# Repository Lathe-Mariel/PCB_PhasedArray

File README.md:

# PCB_PhasedArray

 # BoM
デュアルＭＯＳＦＥＴ（Ｎｃｈ＋Ｎｃｈ）　３０Ｖ５Ａ　ＮＤＳ９９３６　（１０個入）
[NDS9936]

RoHS2未調査、または調査継続中。
ハーフブリッジゲートドライバ　ＩＲ２１５３１ＳＰＢＦＴＲ　ＯＳＣ　８－ＳＯＩＣ（２個入）
[IR21531SPBFTR]

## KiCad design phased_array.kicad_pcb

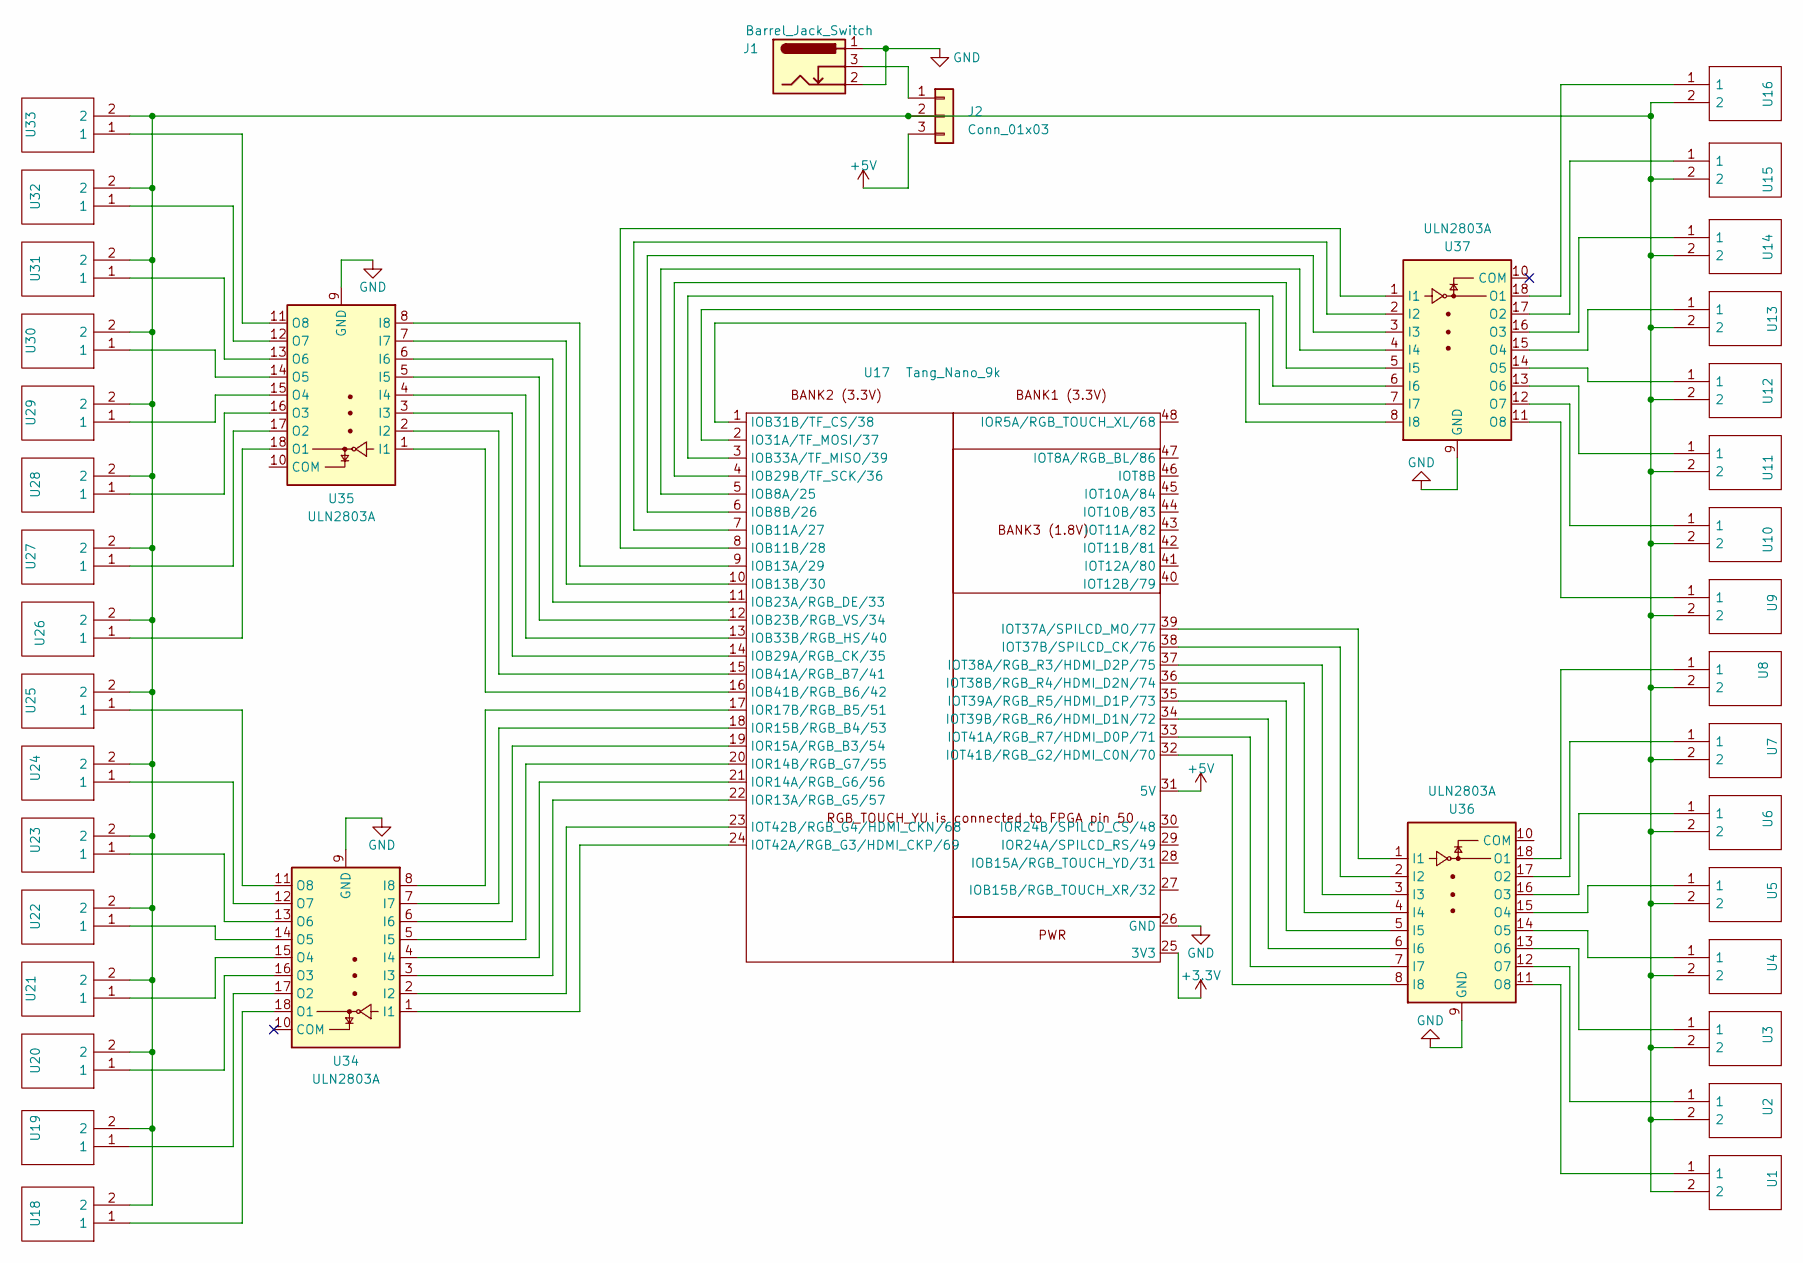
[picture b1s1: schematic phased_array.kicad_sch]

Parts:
J1: Barrel_Jack_Switch; BarrelJack_Horizontal
J2: Conn_01x03; PinHeader_1x03_P2.54mm_Vertical
U1, U2, U3, U4, U5, U6, U7, U8, U9, U10, U11, U12, U13, U14, U15, U16, U18, U19, U20, U21, U22, U23, U24, U25, U26, U27, U28, U29, U30, U31, U32, U33: CUSA-T80-18-2400-TH; CUSAT80182400TH; Manufacturer_Part_Number CUSA-T80-18-2400-TH
U17: Tang_Nano_9k; Tang Nano 9K
U34, U35, U36, U37: ULN2803A; DIP762W55P254L2286H480Q18N_with_solderjumper

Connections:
+3.3V: U17.25 (3V3)
+5V: J2.3, U17.31 (5V)
GND: J1.1, J1.2, U17.26 (GND), U34.9 (GND), U35.9 (GND), U36.9 (GND), U37.9 (GND)
unnamed: J1.3, J2.1
unnamed: J2.2, U1.2, U2.2, U3.2, U4.2, U5.2, U6.2, U7.2, U8.2, U9.2, U10.2, U11.2, U12.2, U13.2, U14.2, U15.2, U16.2, U18.2, U19.2, U20.2, U21.2, U22.2, U23.2, U24.2, U25.2, U26.2, U27.2, U28.2, U29.2, U30.2, U31.2, U32.2, U33.2
unnamed: U17.2 (IO31A/TF_MOSI/37), U37.7 (I7)
unnamed: U17.5 (IOB8A/25), U37.4 (I4)
unnamed: U17.6 (IOB8B/26), U37.3 (I3)
unnamed: U17.7 (IOB11A/27), U37.2 (I2)
unnamed: U17.8 (IOB11B/28), U37.1 (I1)
unnamed: U17.9 (IOB13A/29), U35.8 (I8)
unnamed: U17.10 (IOB13B/30), U35.7 (I7)
unnamed: U17.11 (IOB23A/RGB_DE/33), U35.6 (I6)
unnamed: U17.12 (IOB23B/RGB_VS/34), U35.5 (I5)
unnamed: U17.14 (IOB29A/RGB_CK/35), U35.3 (I3)
unnamed: U17.4 (IOB29B/TF_SCK/36), U37.5 (I5)
unnamed: U17.1 (IOB31B/TF_CS/38), U37.8 (I8)
unnamed: U17.3 (IOB33A/TF_MISO/39), U37.6 (I6)
unnamed: U17.13 (IOB33B/RGB_HS/40), U35.4 (I4)
unnamed: U17.15 (IOB41A/RGB_B7/41), U35.2 (I2)
unnamed: U17.16 (IOB41B/RGB_B6/42), U35.1 (I1)
unnamed: U17.22 (IOR13A/RGB_G5/57), U34.3 (I3)
unnamed: U17.21 (IOR14A/RGB_G6/56), U34.4 (I4)
unnamed: U17.20 (IOR14B/RGB_G7/55), U34.5 (I5)
unnamed: U17.19 (IOR15A/RGB_B3/54), U34.6 (I6)
unnamed: U17.18 (IOR15B/RGB_B4/53), U34.7 (I7)
unnamed: U17.17 (IOR17B/RGB_B5/51), U34.8 (I8)
unnamed: U17.39 (IOT37A/SPILCD_MO/77), U36.1 (I1)
unnamed: U17.38 (IOT37B/SPILCD_CK/76), U36.2 (I2)
unnamed: U17.37 (IOT38A/RGB_R3/HDMI_D2P/75), U36.3 (I3)
unnamed: U17.36 (IOT38B/RGB_R4/HDMI_D2N/74), U36.4 (I4)
unnamed: U17.35 (IOT39A/RGB_R5/HDMI_D1P/73), U36.5 (I5)
unnamed: U17.34 (IOT39B/RGB_R6/HDMI_D1N/72), U36.6 (I6)
unnamed: U17.33 (IOT41A/RGB_R7/HDMI_D0P/71), U36.7 (I7)
unnamed: U17.32 (IOT41B/RGB_G2/HDMI_C0N/70), U36.8 (I8)
unnamed: U17.24 (IOT42A/RGB_G3/HDMI_CKP/69), U34.1 (I1)
unnamed: U17.23 (IOT42B/RGB_G4/HDMI_CKN/68), U34.2 (I2)
unnamed: U18.1, U34.18 (O1)
unnamed: U19.1, U34.17 (O2)
unnamed: U20.1, U34.16 (O3)
unnamed: U21.1, U34.15 (O4)
unnamed: U22.1, U34.14 (O5)
unnamed: U23.1, U34.13 (O6)
unnamed: U24.1, U34.12 (O7)
unnamed: U25.1, U34.11 (O8)
unnamed: U26.1, U35.18 (O1)
unnamed: U27.1, U35.17 (O2)
unnamed: U28.1, U35.16 (O3)
unnamed: U29.1, U35.15 (O4)
unnamed: U30.1, U35.14 (O5)
unnamed: U31.1, U35.13 (O6)
unnamed: U32.1, U35.12 (O7)
unnamed: U33.1, U35.11 (O8)
unnamed: U8.1, U36.18 (O1)
unnamed: U7.1, U36.17 (O2)
unnamed: U6.1, U36.16 (O3)
unnamed: U5.1, U36.15 (O4)
unnamed: U4.1, U36.14 (O5)
unnamed: U3.1, U36.13 (O6)
unnamed: U2.1, U36.12 (O7)
unnamed: U1.1, U36.11 (O8)
unnamed: U16.1, U37.18 (O1)
unnamed: U15.1, U37.17 (O2)
unnamed: U14.1, U37.16 (O3)
unnamed: U13.1, U37.15 (O4)
unnamed: U12.1, U37.14 (O5)
unnamed: U11.1, U37.13 (O6)
unnamed: U10.1, U37.12 (O7)
unnamed: U9.1, U37.11 (O8)

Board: 2 copper layers, 39 parts (6 on the bottom side), 68 nets, no tracks yet.

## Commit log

2023-10-13 1014
2023-10-14 1015
2023-10-16 1017
2023-10-26 1026
